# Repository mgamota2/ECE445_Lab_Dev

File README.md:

# PCB Design Assignment for Senior Design (ECE 445)

This tutorial: `instructions.pdf` describes how to design and test an STM32 based "dev board", with an on-board H bridge IC to allow for rapid motor control application prototyping.

An example board is found in the `stm32_cad` folder

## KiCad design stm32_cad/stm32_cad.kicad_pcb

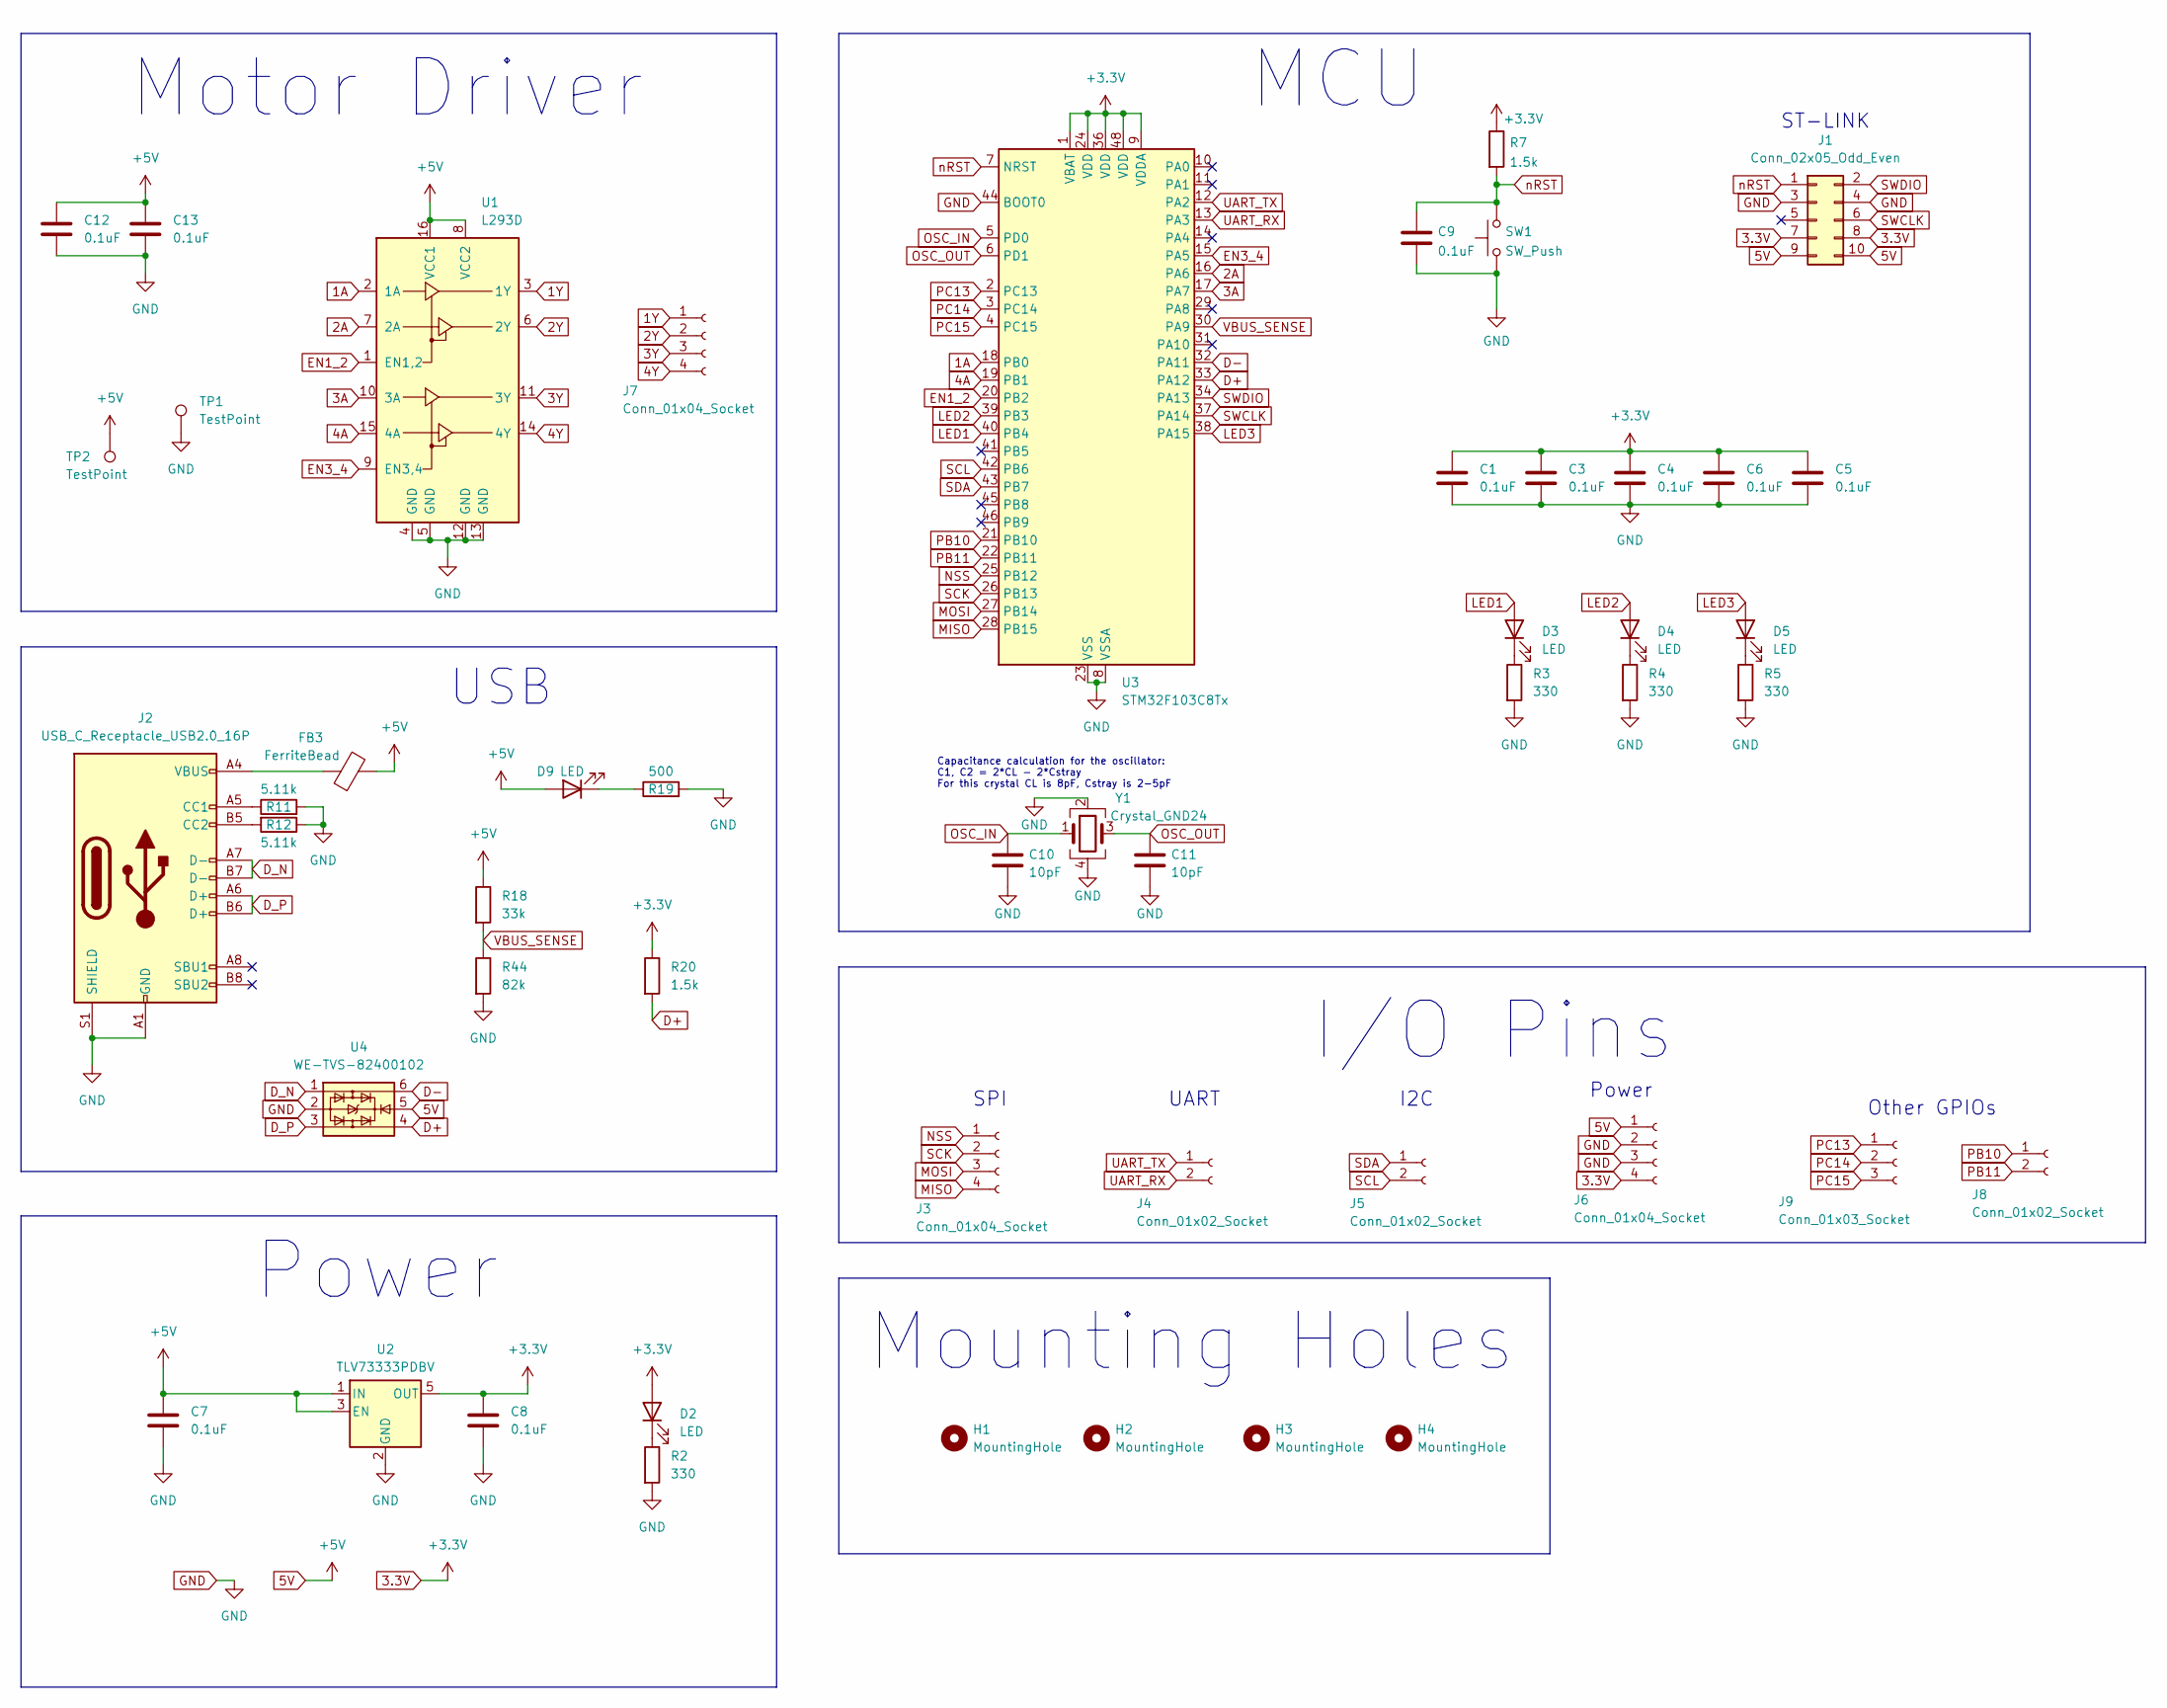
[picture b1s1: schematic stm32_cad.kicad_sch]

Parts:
C1, C3, C4, C5, C6, C7, C8, C9, C12, C13: 0.1uF; C_0805_2012Metric
C10, C11: 10pF; C_0805_2012Metric
D2, D3, D4, D5, D9: LED; LED_0805_2012Metric
FB3: FerriteBead; R_0805_2012Metric
H1, H2, H3, H4: MountingHole; MountingHole_3.2mm_M3
J1: Conn_02x05_Odd_Even; PinSocket_2x05_P2.54mm_Vertical
J2: USB_C_Receptacle_USB2.0_16P; USB_C_Receptacle_GCT_USB4085
J3, J6, J7: Conn_01x04_Socket; PinSocket_1x04_P2.54mm_Vertical
J4, J5, J8: Conn_01x02_Socket; PinSocket_1x02_P2.54mm_Vertical
J9: Conn_01x03_Socket; PinSocket_1x03_P2.54mm_Vertical
R2, R3, R4, R5: 330; R_0805_2012Metric
R7, R20: 1.5k; R_0805_2012Metric
R11, R12: 5.11k; R_0805_2012Metric
R18: 33k; R_0805_2012Metric
R19: 500; R_0805_2012Metric
R44: 82k; R_0805_2012Metric
SW1: SW_Push; SW_Push_SPST_NO_Alps_SKRK
TP1, TP2: TestPoint; TestPoint_Pad_4.0x4.0mm
U1: L293D; DIP-16_W7.62mm
U2: TLV73333PDBV; SOT-23-5
U3: STM32F103C8Tx; LQFP-48_7x7mm_P0.5mm
U4: WE-TVS-82400102; SOT-23-6
Y1: Crystal_GND24; Crystal_SMD_5032-4Pin_5.0x3.2mm

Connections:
1A: U1.2 (1A), U3.18 (PB0)
1Y: J7.1, U1.3 (1Y)
2A: U1.7 (2A), U3.16 (PA6)
2Y: J7.2, U1.6 (2Y)
3.3V: C1.1, C3.1, C4.1, C5.1, C6.1, C8.1, D2.2 (A), J1.7, J1.8, J6.4, R7.1, R20.1, U2.5 (OUT), U3.1 (VBAT), U3.9 (VDDA), U3.24 (VDD), U3.36 (VDD), U3.48 (VDD)
3A: U1.10 (3A), U3.17 (PA7)
3Y: J7.3, U1.11 (3Y)
4A: U1.15 (4A), U3.19 (PB1)
4Y: J7.4, U1.14 (4Y)
5V: C7.1, C12.1, C13.1, D9.2 (A), FB3.2, J1.9, J1.10, J6.1, R18.1, TP2.1, U1.8 (VCC2), U1.16 (VCC1), U2.1 (IN), U2.3 (EN), U4.5
D+: R20.2, U3.33 (PA12), U4.4
D-: U3.32 (PA11), U4.6
D_N: J2.A7 (D-), J2.B7 (D-), U4.1
D_P: J2.A6 (D+), J2.B6 (D+), U4.3
EN1_2: U1.1 (EN1,2), U3.20 (PB2)
EN3_4: U1.9 (EN3,4), U3.15 (PA5)
GND: C1.2, C3.2, C4.2, C5.2, C6.2, C7.2, C8.2, C9.2, C10.2, C11.2, C12.2, C13.2, J1.3, J1.4, J2.A1 (GND), J2.A12 (GND), J2.B1 (GND), J2.B12 (GND), J2.S1 (SHIELD), J6.2, J6.3, R2.2, R3.2, R4.2, R5.2, R11.2, R12.1, R19.2, R44.2, SW1.1, TP1.1, U1.4 (GND), U1.5 (GND), U1.12 (GND), U1.13 (GND), U2.2 (GND), U3.8 (VSSA), U3.23 (VSS), U3.35 (VSS), U3.44 (BOOT0), U3.47 (VSS), U4.2, Y1.2, Y1.4
LED1: D3.2 (A), U3.40 (PB4)
LED2: D4.2 (A), U3.39 (PB3)
LED3: D5.2 (A), U3.38 (PA15)
MISO: J3.4, U3.28 (PB15)
MOSI: J3.3, U3.27 (PB14)
NSS: J3.1, U3.25 (PB12)
unnamed: D2.1 (K), R2.1
unnamed: D3.1 (K), R3.1
unnamed: D4.1 (K), R4.1
unnamed: D5.1 (K), R5.1
unnamed: D9.1 (K), R19.1
unnamed: FB3.1, J2.A4 (VBUS), J2.A9 (VBUS), J2.B4 (VBUS), J2.B9 (VBUS)
unnamed: J2.A5 (CC1), R11.1
unnamed: J2.B5 (CC2), R12.2
OSC_IN: C10.1, U3.5 (PD0), Y1.1
OSC_OUT: C11.1, U3.6 (PD1), Y1.3
PB10: J8.1, U3.21 (PB10)
PB11: J8.2, U3.22 (PB11)
PC13: J9.1, U3.2 (PC13)
PC14: J9.2, U3.3 (PC14)
PC15: J9.3, U3.4 (PC15)
SCK: J3.2, U3.26 (PB13)
SCL: J5.2, U3.42 (PB6)
SDA: J5.1, U3.43 (PB7)
SWCLK: J1.6, U3.37 (PA14)
SWDIO: J1.2, U3.34 (PA13)
UART_RX: J4.2, U3.13 (PA3)
UART_TX: J4.1, U3.12 (PA2)
VBUS_SENSE: R18.2, R44.1, U3.30 (PA9)
nRST: C9.1, J1.1, R7.2, SW1.2, U3.7 (NRST)

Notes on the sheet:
MCU
SPI
Motor Driver
I2C
I/O Pins
Power
Capacitance calculation for the oscillator: C1, C2 = 2*CL - 2*Cstray For this crystal CL is 8pF, Cstray is 2-5pF
Power
USB
UART
Other GPIOs
ST-LINK
Mounting Holes

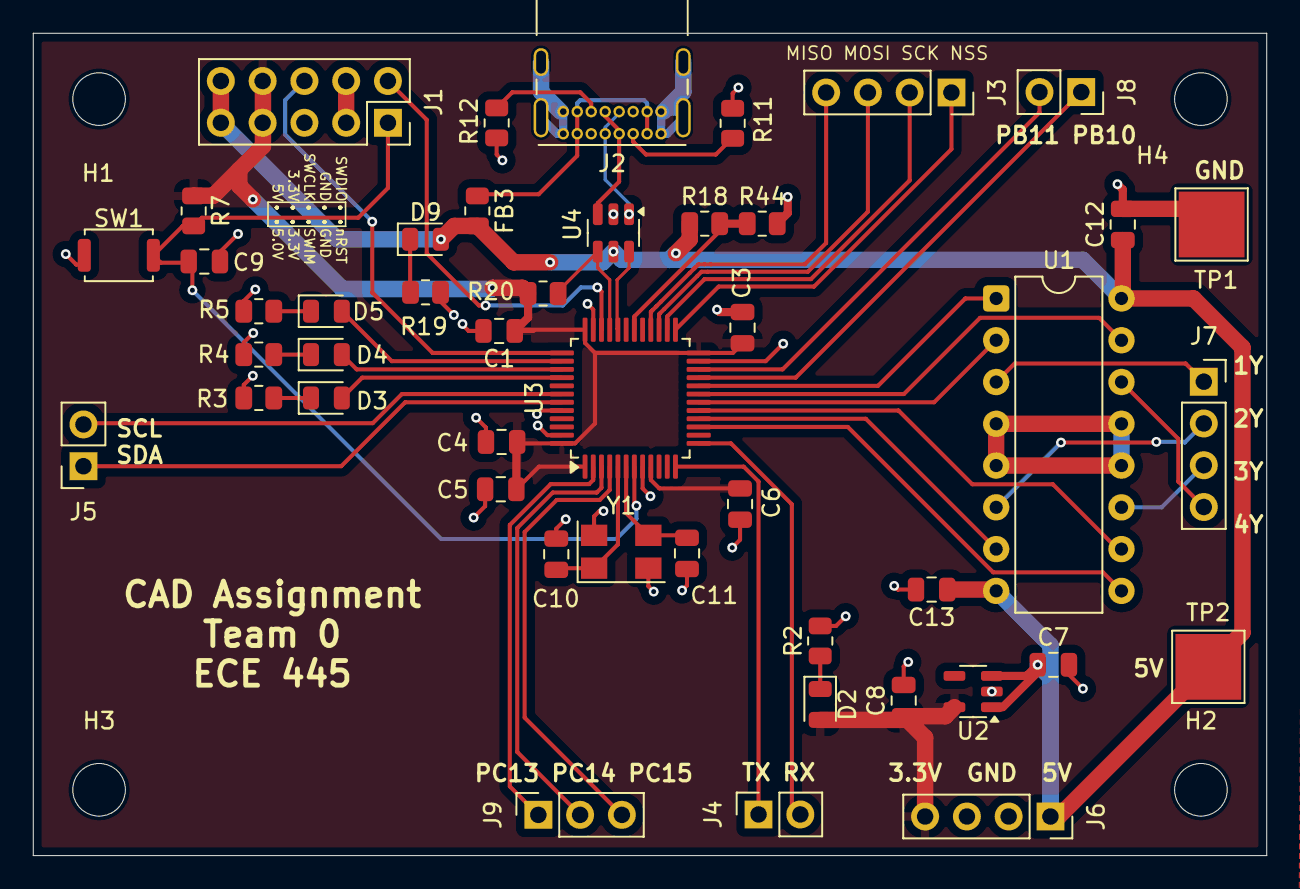
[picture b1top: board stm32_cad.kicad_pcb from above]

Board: 2 copper layers, 75.0 x 50.0 mm, 50 parts (0 on the bottom side), 47 nets.

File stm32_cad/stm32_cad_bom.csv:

"Reference","Value","Datasheet","Footprint","Qty","DNP"
"C1,C3,C4,C5,C6,C7,C8,C9,C12,C13","0.1uF","~","Capacitor_SMD:C_0805_2012Metric","10",""
"C10,C11","10pF","~","Capacitor_SMD:C_0805_2012Metric","2",""
"D2,D3,D4,D5,D9","LED","~","LED_SMD:LED_0805_2012Metric","5",""
"FB3","FerriteBead","~","Resistor_SMD:R_0805_2012Metric","1",""
"H1,H2,H3,H4","MountingHole","~","MountingHole:MountingHole_3.2mm_M3","4",""
"J1","Conn_02x05_Odd_Even","~","Connector_PinSocket_2.54mm:PinSocket_2x05_P2.54mm_Vertical","1",""
"J2","USB_C_Receptacle_USB2.0_16P","https://www.usb.org/sites/default/files/documents/usb_type-c.zip","Connector_USB:USB_C_Receptacle_GCT_USB4085","1",""
"J3,J6,J7","Conn_01x04_Socket","~","Connector_PinSocket_2.54mm:PinSocket_1x04_P2.54mm_Vertical","3",""
"J4,J5,J8","Conn_01x02_Socket","~","Connector_PinSocket_2.54mm:PinSocket_1x02_P2.54mm_Vertical","3",""
"J9","Conn_01x03_Socket","~","Connector_PinSocket_2.54mm:PinSocket_1x03_P2.54mm_Vertical","1",""
"R2,R3,R4,R5","330","~","Resistor_SMD:R_0805_2012Metric","4",""
"R7","1K","~","Resistor_SMD:R_0805_2012Metric","1",""
"R11,R12","5.11k","~","Resistor_SMD:R_0805_2012Metric","2",""
"R18","33k","~","Resistor_SMD:R_0805_2012Metric","1",""
"R19","500","~","Resistor_SMD:R_0805_2012Metric","1",""
"R20","1.5k","~","Resistor_SMD:R_0805_2012Metric","1",""
"R44","82k","~","Resistor_SMD:R_0805_2012Metric","1",""
"SW1","SW_Push","~","Button_Switch_SMD:SW_Push_SPST_NO_Alps_SKRK","1",""
"TP1,TP2","TestPoint","~","TestPoint:TestPoint_Pad_4.0x4.0mm","2",""
"U1","L293D","http://www.ti.com/lit/ds/symlink/l293.pdf","Package_DIP:DIP-16_W7.62mm","1",""
"U2","TLV73333PDBV","http://www.ti.com/lit/ds/symlink/tlv733p.pdf","Package_TO_SOT_SMD:SOT-23-5","1",""
"U3","STM32F103C8Tx","https://www.st.com/resource/en/datasheet/stm32f103c8.pdf","Package_QFP:LQFP-48_7x7mm_P0.5mm","1",""
"U4","WE-TVS-82400102","https://www.we-online.com/components/products/datasheet/8240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","Package_TO_SOT_SMD:SOT-23-6","1",""
"Y1","Crystal_GND24","~","Crystal:Crystal_SMD_5032-4Pin_5.0x3.2mm","1",""

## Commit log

2025-08-24 Added readme
